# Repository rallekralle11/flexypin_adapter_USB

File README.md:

Because why not use the native USB when the module has it?

For sale now.

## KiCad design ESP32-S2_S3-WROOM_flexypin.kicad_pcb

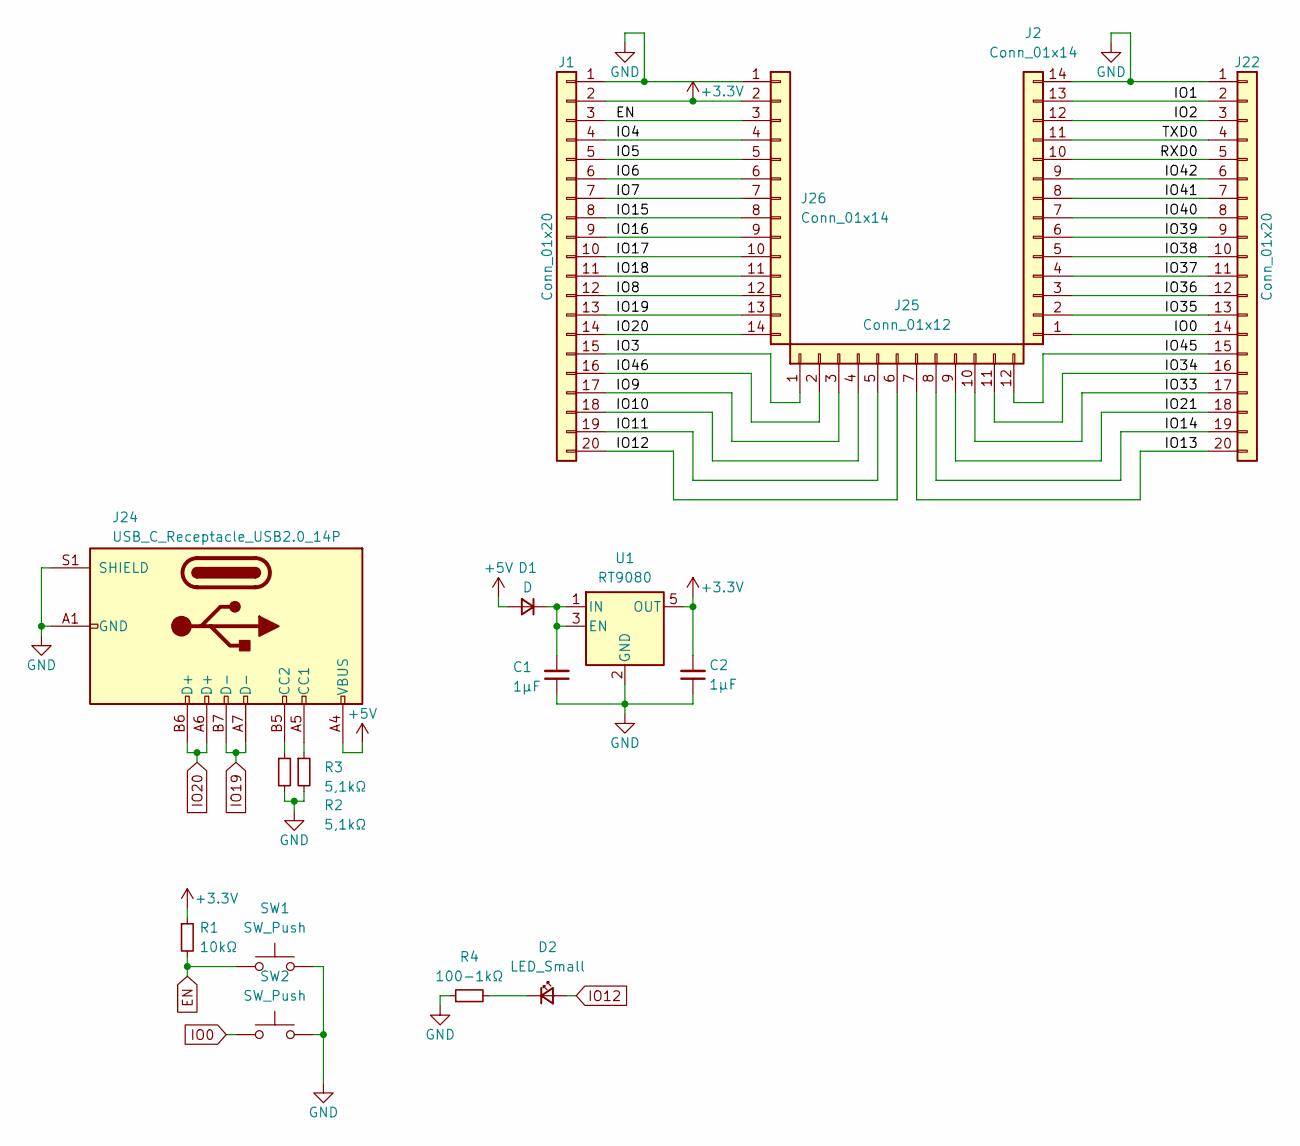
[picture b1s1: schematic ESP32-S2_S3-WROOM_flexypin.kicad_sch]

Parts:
C1, C2: 1µF; C_0402_1005Metric
D1: D; D_SOD-323
D2: LED_Small; LED_0402_1005Metric
J1, J22: Conn_01x20; PinHeader_1x20_P2.54mm_Vertical
J2, J26: Conn_01x14; FlexyPin_1x14_P1.27mm
J24: USB_C_Receptacle_USB2.0_14P; USB_C_Receptacle_G-Switch_GT-USB-7010ASV
J25: Conn_01x12; FlexyPin_1x12_P1.27mm
R1: 10kΩ; R_0402_1005Metric
R2, R3: 5,1kΩ; R_0402_1005Metric
R4: 100-1kΩ; R_0402_1005Metric
SW1, SW2: SW_Push; SW_Push_SPST_NO_Alps_SKRK
U1: RT9080; SOT-23-5

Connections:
+3.3V: C2.2, J1.2, J26.2, R1.1, U1.5 (OUT)
+5V: D1.2 (A), J24.A4 (VBUS), J24.A9 (VBUS), J24.B4 (VBUS), J24.B9 (VBUS)
/IO1: J2.13, J22.2
/IO2: J2.12, J22.3
/IO3: J1.15, J25.1
/IO4: J1.4, J26.4
/IO5: J1.5, J26.5
/IO6: J1.6, J26.6
/IO7: J1.7, J26.7
/IO8: J1.12, J26.12
/IO9: J1.17, J25.3
/IO10: J1.18, J25.4
/IO11: J1.19, J25.5
/IO13: J22.20, J25.7
/IO14: J22.19, J25.8
/IO15: J1.8, J26.8
/IO16: J1.9, J26.9
/IO17: J1.10, J26.10
/IO18: J1.11, J26.11
/IO21: J22.18, J25.9
/IO33: J22.17, J25.10
/IO34: J22.16, J25.11
/IO35: J2.2, J22.13
/IO36: J2.3, J22.12
/IO37: J2.4, J22.11
/IO38: J2.5, J22.10
/IO39: J2.6, J22.9
/IO40: J2.7, J22.8
/IO41: J2.8, J22.7
/IO42: J2.9, J22.6
/IO45: J22.15, J25.12
/IO46: J1.16, J25.2
/RXD0: J2.10, J22.5
/TXD0: J2.11, J22.4
EN: J1.3, J26.3, R1.2, SW1.1
GND: C1.1, C2.1, J1.1, J2.14, J22.1, J24.A1 (GND), J24.A12 (GND), J24.B1 (GND), J24.B12 (GND), J24.S1 (SHIELD), J26.1, R2.2, R3.2, R4.1, SW1.2, SW2.2, U1.2 (GND)
IO0: J2.1, J22.14, SW2.1
IO12: D2.2 (A), J1.20, J25.6
IO19: J1.13, J24.A7 (D-), J24.B7 (D-), J26.13
IO20: J1.14, J24.A6 (D+), J24.B6 (D+), J26.14
unnamed: C1.2, D1.1 (K), U1.1 (IN), U1.3 (EN)
unnamed: D2.1 (K), R4.2
unnamed: J24.A5 (CC1), R3.1
unnamed: J24.B5 (CC2), R2.1

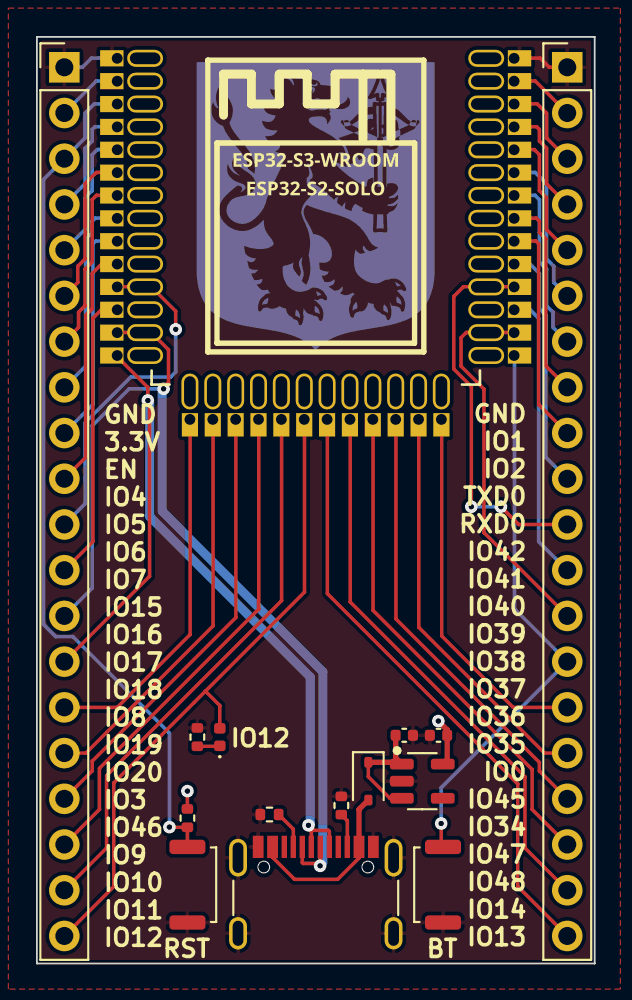
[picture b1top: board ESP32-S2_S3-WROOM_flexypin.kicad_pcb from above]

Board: 2 copper layers, 31.0 x 51.5 mm, 17 parts (0 on the bottom side), 44 nets.

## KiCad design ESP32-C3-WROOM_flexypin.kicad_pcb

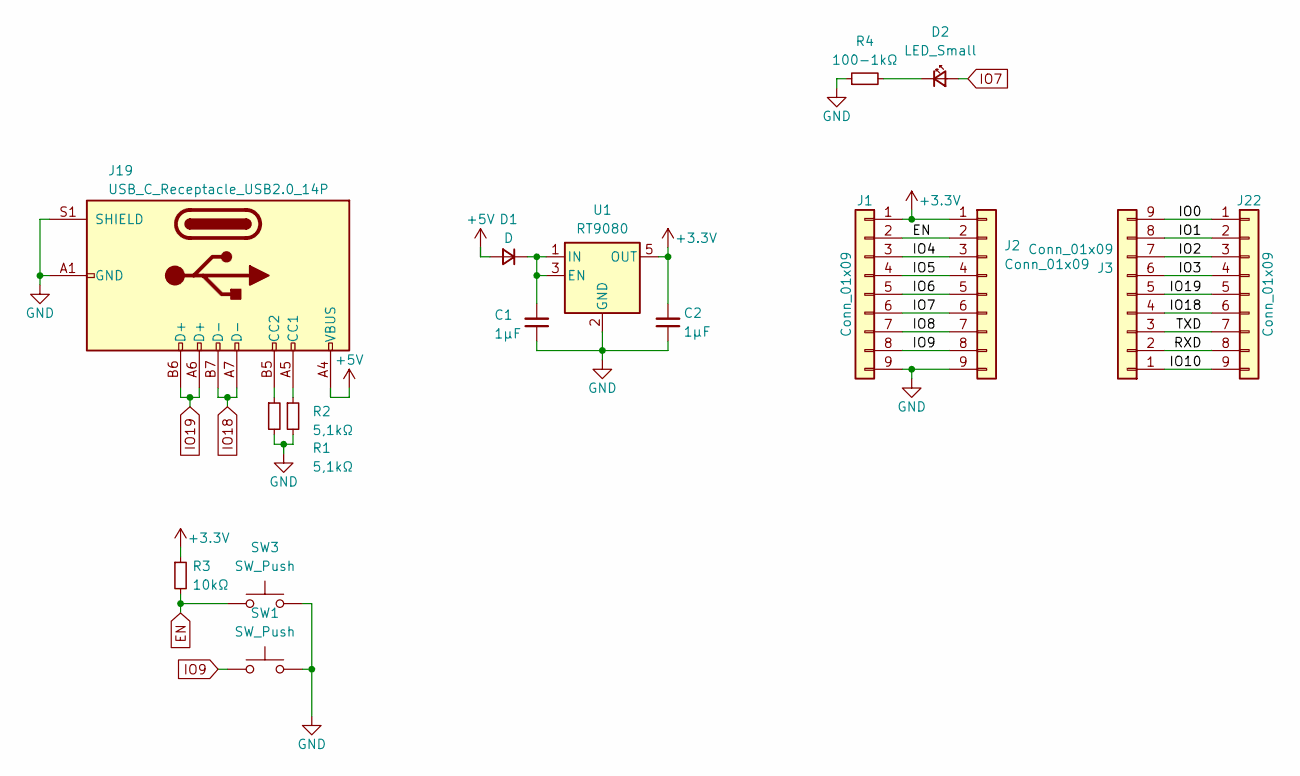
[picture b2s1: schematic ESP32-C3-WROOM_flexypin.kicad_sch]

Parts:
C1, C2: 1µF; C_0402_1005Metric
D1: D; D_SOD-323
D2: LED_Small; LED_0402_1005Metric
J1, J22: Conn_01x09; PinHeader_1x09_P2.54mm_Vertical
J2, J3: Conn_01x09; FlexyPin_1x09_P1.50mm
J19: USB_C_Receptacle_USB2.0_14P; USB_C_Receptacle_G-Switch_GT-USB-7010ASV
R1, R2: 5,1kΩ; R_0402_1005Metric
R3: 10kΩ; R_0402_1005Metric
R4: 100-1kΩ; R_0402_1005Metric
SW1, SW3: SW_Push; SW_Push_SPST_NO_Alps_SKRK
U1: RT9080; SOT-23-5

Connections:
+3.3V: C2.2, J1.1, J2.1, R3.1, U1.5 (OUT)
+5V: D1.2 (A), J19.A4 (VBUS), J19.A9 (VBUS), J19.B4 (VBUS), J19.B9 (VBUS)
/IO0: J3.9, J22.1
/IO1: J3.8, J22.2
/IO2: J3.7, J22.3
/IO3: J3.6, J22.4
/IO4: J1.3, J2.3
/IO5: J1.4, J2.4
/IO6: J1.5, J2.5
/IO8: J1.7, J2.7
/IO10: J3.1, J22.9
/RXD: J3.2, J22.8
/TXD: J3.3, J22.7
EN: J1.2, J2.2, R3.2, SW3.1
GND: C1.1, C2.1, J1.9, J2.9, J19.A1 (GND), J19.A12 (GND), J19.B1 (GND), J19.B12 (GND), J19.S1 (SHIELD), R1.2, R2.2, R4.1, SW1.2, SW3.2, U1.2 (GND)
IO7: D2.2 (A), J1.6, J2.6
IO9: J1.8, J2.8, SW1.1
IO18: J3.4, J19.A7 (D-), J19.B7 (D-), J22.6
IO19: J3.5, J19.A6 (D+), J19.B6 (D+), J22.5
unnamed: C1.2, D1.1 (K), U1.1 (IN), U1.3 (EN)
unnamed: D2.1 (K), R4.2
unnamed: J19.A5 (CC1), R2.1
unnamed: J19.B5 (CC2), R1.1

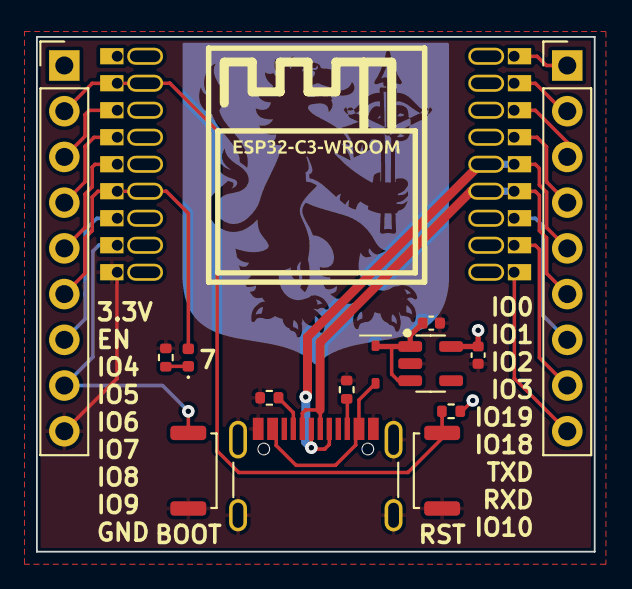
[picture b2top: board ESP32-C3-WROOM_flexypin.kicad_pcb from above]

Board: 2 copper layers, 31.0 x 28.6 mm, 16 parts (0 on the bottom side), 23 nets.

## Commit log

2024-08-16 init
2024-08-16 added S2-3
2024-08-17 made the C3
2024-08-17 picture
2024-08-17 better picture
2024-08-17 gerbers
2024-08-19 schematic etc
2024-08-30 added LED
2024-09-24 mislabeling
